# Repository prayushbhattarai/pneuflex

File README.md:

# PneuFlex

A wearable pneumatic prototype designed to assist elbow flexion during upper-limb rehabilitation. Combines soft robotics, custom electronics, and a React companion app.

## How It Works

A flex sensor measures bending while an ESP32 controls an air pump. Air pressure contracts a McKibben actuator to assist elbow movement.

Intent recognition aims to interpret flex-sensor patterns to identify attempted movement and provide assistance when needed.

## Hardware

- ESP32 and flex sensor
- McKibben actuator and 12 V pump
- MOSFET pump driver
- LiPo battery and boost converter
- Custom two-layer PCB, sleeve, and enclosure

## Software

- Embedded firmware for sensing and pump control
- Movement-intent recognition from sensor data
- React app with patient dashboard, goals, session history, and therapist views

## Recognition

Developed by a four-person team. **3rd place in Medical Innovation at the 2026 HOSA International Leadership Conference.**

## Status

Experimental prototype. Ongoing improvements focus on sensing, intent recognition, pneumatic control, and app integration. Not clinically validated.

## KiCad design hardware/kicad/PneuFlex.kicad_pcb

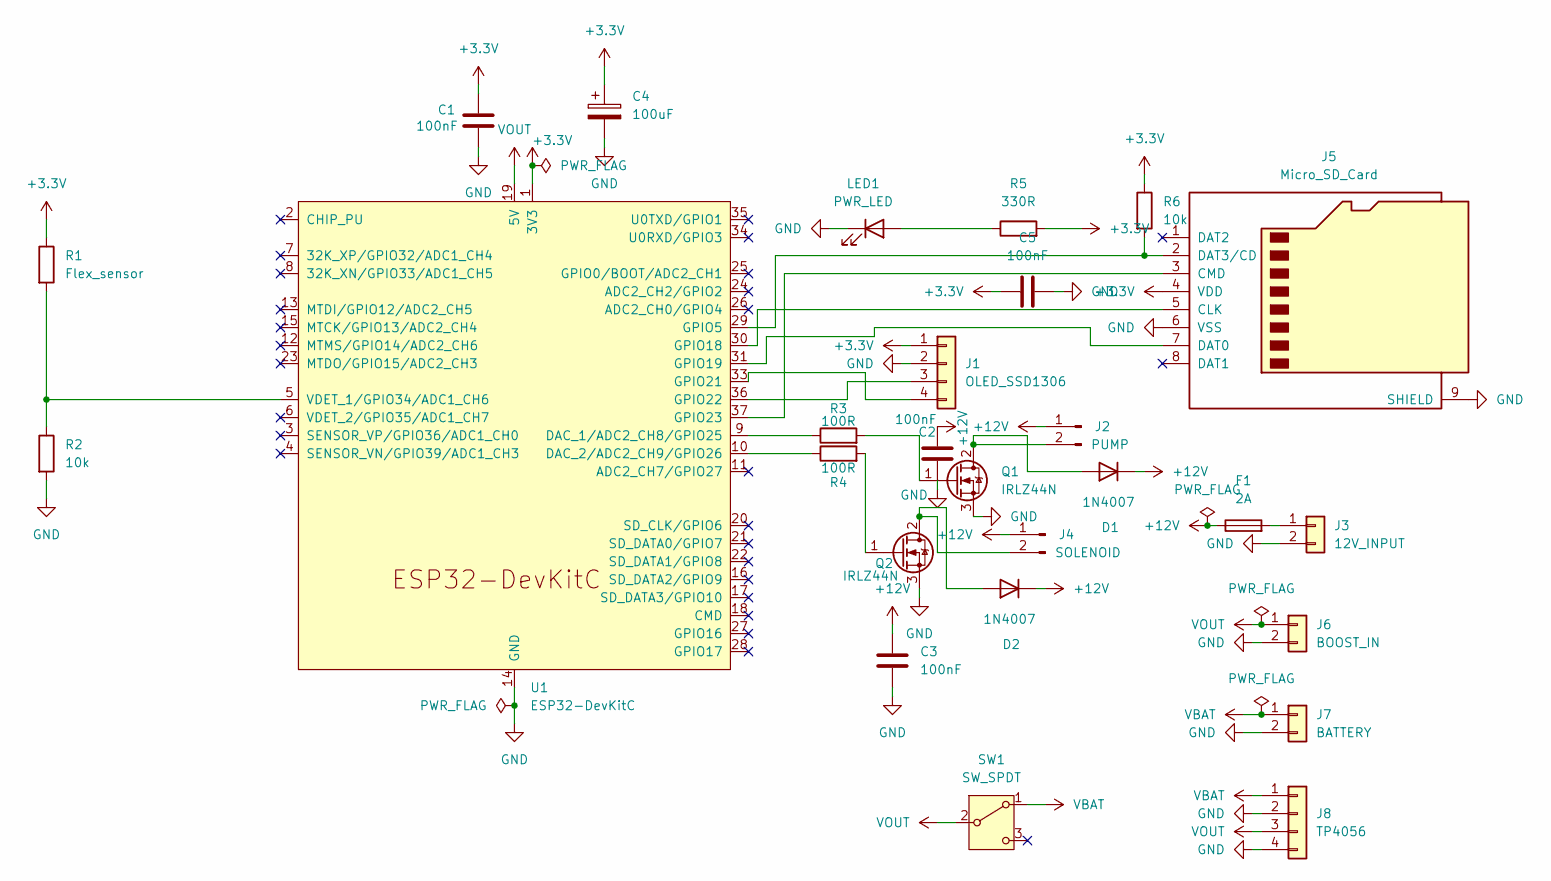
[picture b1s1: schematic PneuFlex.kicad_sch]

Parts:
C1, C2, C3, C5: 100nF; C_Disc_D5.0mm_W2.5mm_P2.50mm
C4: 100uF; CP_Radial_D6.3mm_P2.50mm
D1, D2: 1N4007; D_DO-41_SOD81_P10.16mm_Horizontal
F1: 2A; R_Axial_DIN0207_L6.3mm_D2.5mm_P10.16mm_Horizontal
J1: OLED_SSD1306; PinHeader_1x04_P2.54mm_Vertical
J2: PUMP; PinHeader_1x02_P2.54mm_Vertical
J3: 12V_INPUT; TerminalBlock_Phoenix_PT-1,5-2-5.0-H_1x02_P5.00mm_Horizontal
J4: SOLENOID; PinHeader_1x02_P2.54mm_Vertical
J5: Micro_SD_Card; microSD_HC_Molex_104031-0811
J6: BOOST_IN; TerminalBlock_Phoenix_PT-1,5-2-5.0-H_1x02_P5.00mm_Horizontal
J7: BATTERY; JST_PH_B2B-PH-K_1x02_P2.00mm_Vertical
J8: TP4056; PinHeader_1x04_P2.54mm_Vertical
LED1: PWR_LED; LED_D3.0mm
Q1, Q2: IRLZ44N; TO-220-3_Vertical
R1: Flex_sensor; PinHeader_1x02_P2.54mm_Vertical
R2, R6: 10k; R_Axial_DIN0207_L6.3mm_D2.5mm_P10.16mm_Horizontal
R3, R4: 100R; R_Axial_DIN0207_L6.3mm_D2.5mm_P10.16mm_Horizontal
R5: 330R; R_Axial_DIN0207_L6.3mm_D2.5mm_P10.16mm_Horizontal
SW1: SW_SPDT; SW_Slide_SPDT_Straight_CK_OS102011MS2Q
U1: ESP32-DevKitC

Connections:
+3.3V: C1.1, C4.1, C5.1, J1.1, J5.4 (VDD), R1.1, R5.2, R6.1, U1.1 (3V3)
+12V: C2.1, C3.1, D1.1 (K), D2.1 (K), F1.1, J2.1, J4.1
GND: C1.2, C2.2, C3.2, C4.2, C5.2, J1.2, J3.2, J5.6 (VSS), J5.9 (SHIELD), J6.2, J7.2, J8.2, J8.4, LED1.1 (K), Q1.3 (S), Q2.3 (S), R2.2, U1.14 (GND), U1.32 (GND), U1.38 (GND)
unnamed: D1.2 (A), J2.2, Q1.2 (D)
unnamed: D2.2 (A), J4.2, Q2.2 (D)
unnamed: J1.3, U1.36 (GPIO22)
unnamed: J1.4, U1.33 (GPIO21)
unnamed: F1.2, J3.1
unnamed: J5.5 (CLK), U1.30 (GPIO18)
unnamed: J5.3 (CMD), U1.37 (GPIO23)
unnamed: J5.7 (DAT0), U1.31 (GPIO19)
unnamed: J5.2 (DAT3/CD), R6.2, U1.29 (GPIO5)
unnamed: LED1.2 (A), R5.1
unnamed: Q1.1 (G), R3.2
unnamed: Q2.1 (G), R4.2
unnamed: R3.1, U1.9 (DAC_1/ADC2_CH8/GPIO25)
unnamed: R4.1, U1.10 (DAC_2/ADC2_CH9/GPIO26)
unnamed: R1.2, R2.1, U1.5 (VDET_1/GPIO34/ADC1_CH6)
VBAT: J7.1, J8.1, SW1.1 (A)
VOUT: J6.1, J8.3, SW1.2 (B), U1.19 (5V)

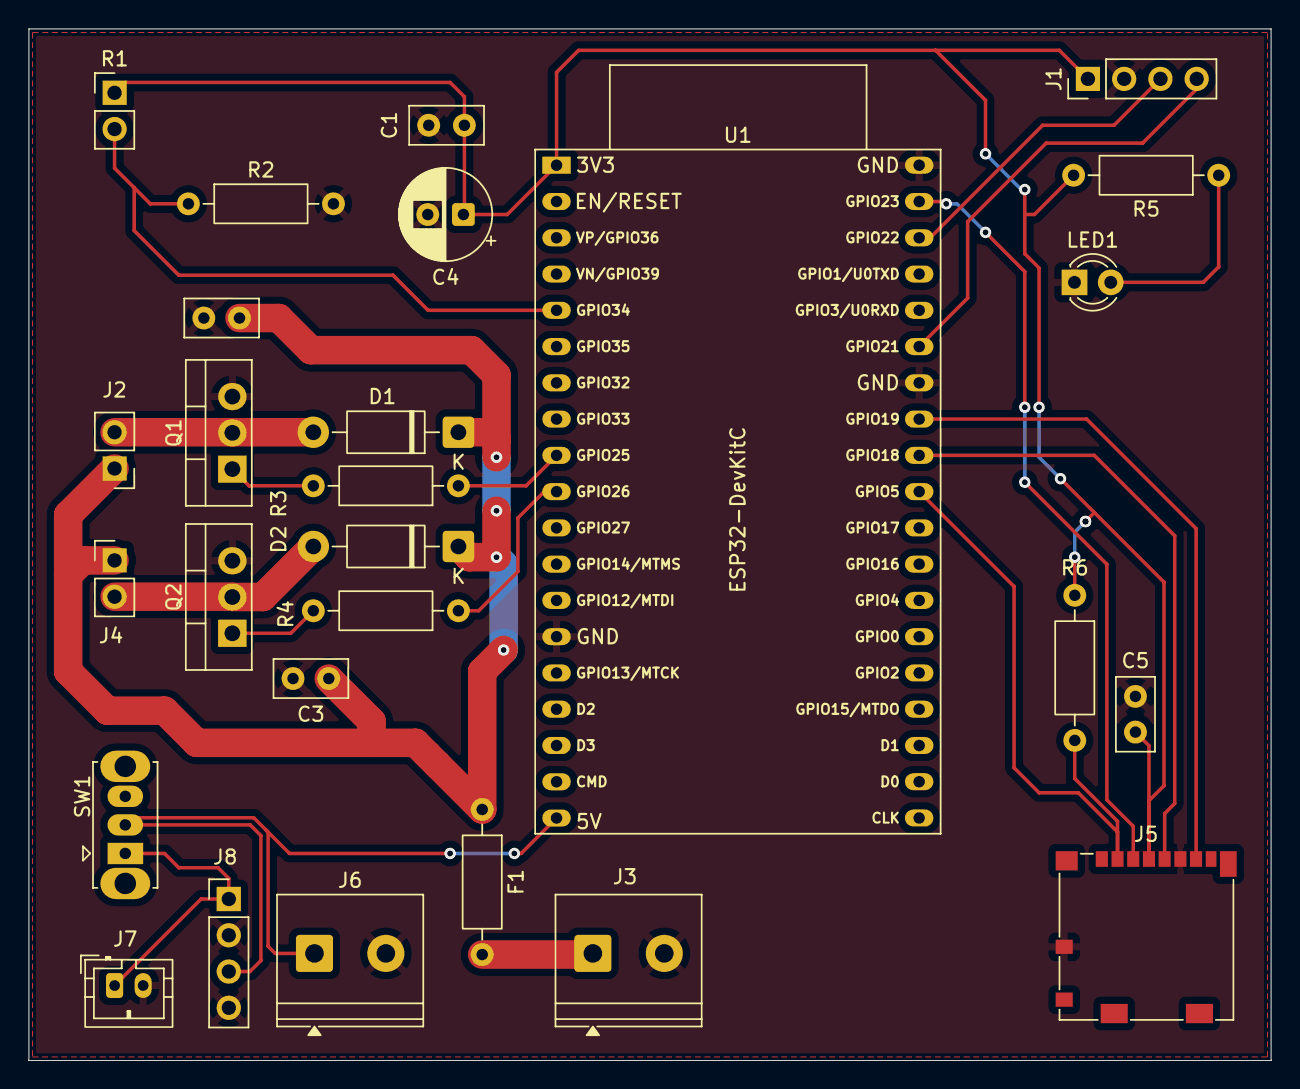
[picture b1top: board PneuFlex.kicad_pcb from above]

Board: 2 copper layers, 87.0 x 72.2 mm, 27 parts (0 on the bottom side), 20 nets.
